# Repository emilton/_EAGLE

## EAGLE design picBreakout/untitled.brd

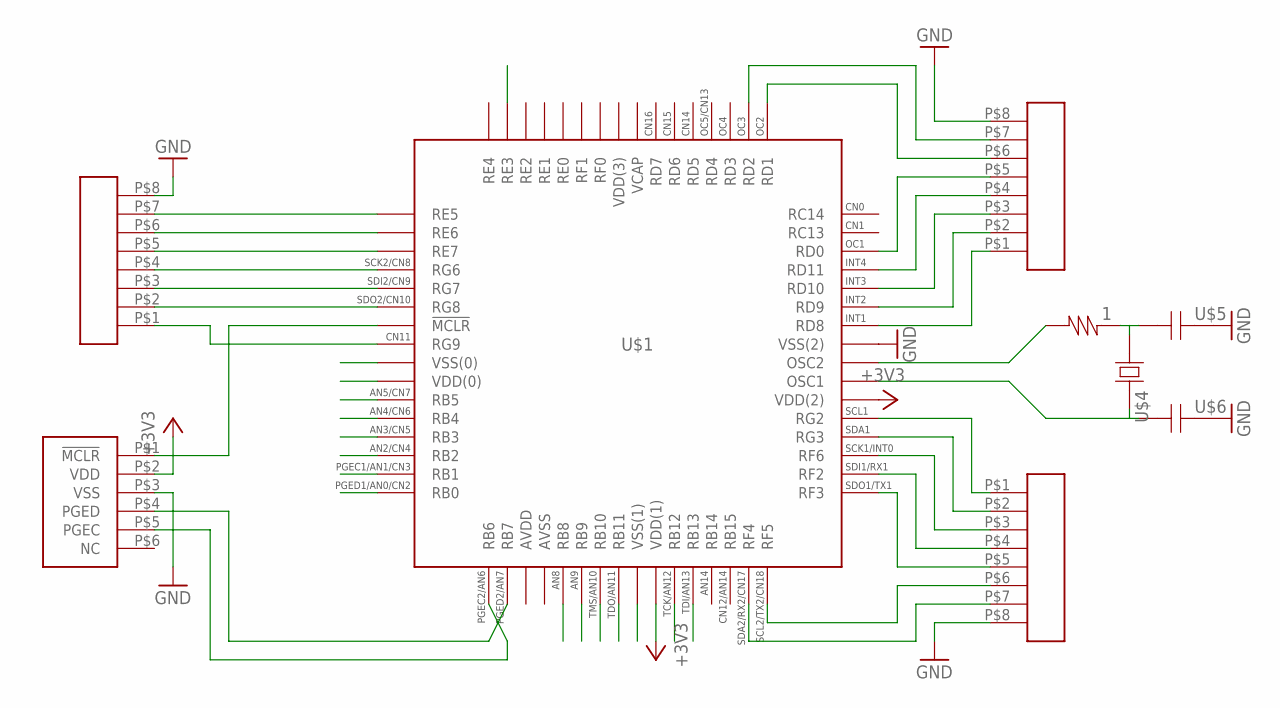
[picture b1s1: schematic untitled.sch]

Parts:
1: .RES-0603; E_0603
U$1: PIC32MX5XX; E_QFN64
U$2, U$3, U$27: CON_8PIN
U$4: .XTAL-CTS406; SMT_CRYSTAL
U$5, U$6: .CAP-0603; E_0603
U$29: CON_ICSP-PIC

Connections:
+3V3: U$1.P$26 (VDD(1)), U$1.P$38 (VDD(2)), U$29.P$2 (VDD)
GND: U$1.P$41 (VSS(2)), U$2.P$8, U$3.P$8, U$5.P$2, U$6.P$2, U$27.P$8, U$29.P$3 (VSS)
unnamed: U$1.P$37 (RG2), U$27.P$1
unnamed: U$1.P$36 (RG3), U$27.P$2
unnamed: U$1.P$35 (RF6), U$27.P$3
unnamed: U$1.P$42 (RD8), U$3.P$1
unnamed: U$1.P$18 (RB7), U$29.P$4 (PGED)
unnamed: U$1.P$6 (RG8), U$2.P$2
unnamed: U$1.P$5 (RG7), U$2.P$3
unnamed: U$1.P$43 (RD9), U$3.P$2
unnamed: U$1.P$44 (RD10), U$3.P$3
unnamed: U$1.P$34 (RF2), U$27.P$4
unnamed: U$1.P$33 (RF3), U$27.P$5
unnamed: U$1.P$32 (RF5), U$27.P$6
unnamed: U$1.P$4 (RG6), U$2.P$4
unnamed: U$1.P$3 (RE7), U$2.P$5
unnamed: U$1.P$49 (RD1), U$3.P$6
unnamed: U$1.P$50 (RD2), U$3.P$7
unnamed: U$1.P$31 (RF4), U$27.P$7
unnamed: U$1.P$45 (RD11), U$3.P$4
unnamed: U$1.P$46 (RD0), U$3.P$5
unnamed: U$1.P$17 (RB6), U$29.P$5 (PGEC)
unnamed: U$1.P$7 (!MCLR), U$29.P$1 (!MCLR)
unnamed: U$1.P$2 (RE6), U$2.P$6
unnamed: U$1.P$1 (RE5), U$2.P$7
unnamed: 1.P$1, U$1.P$40 (OSC2)
unnamed: 1.P$2, U$4.P$1, U$5.P$1
unnamed: U$1.P$39 (OSC1), U$4.P$3, U$6.P$1
unnamed: U$1.P$8 (RG9), U$2.P$1

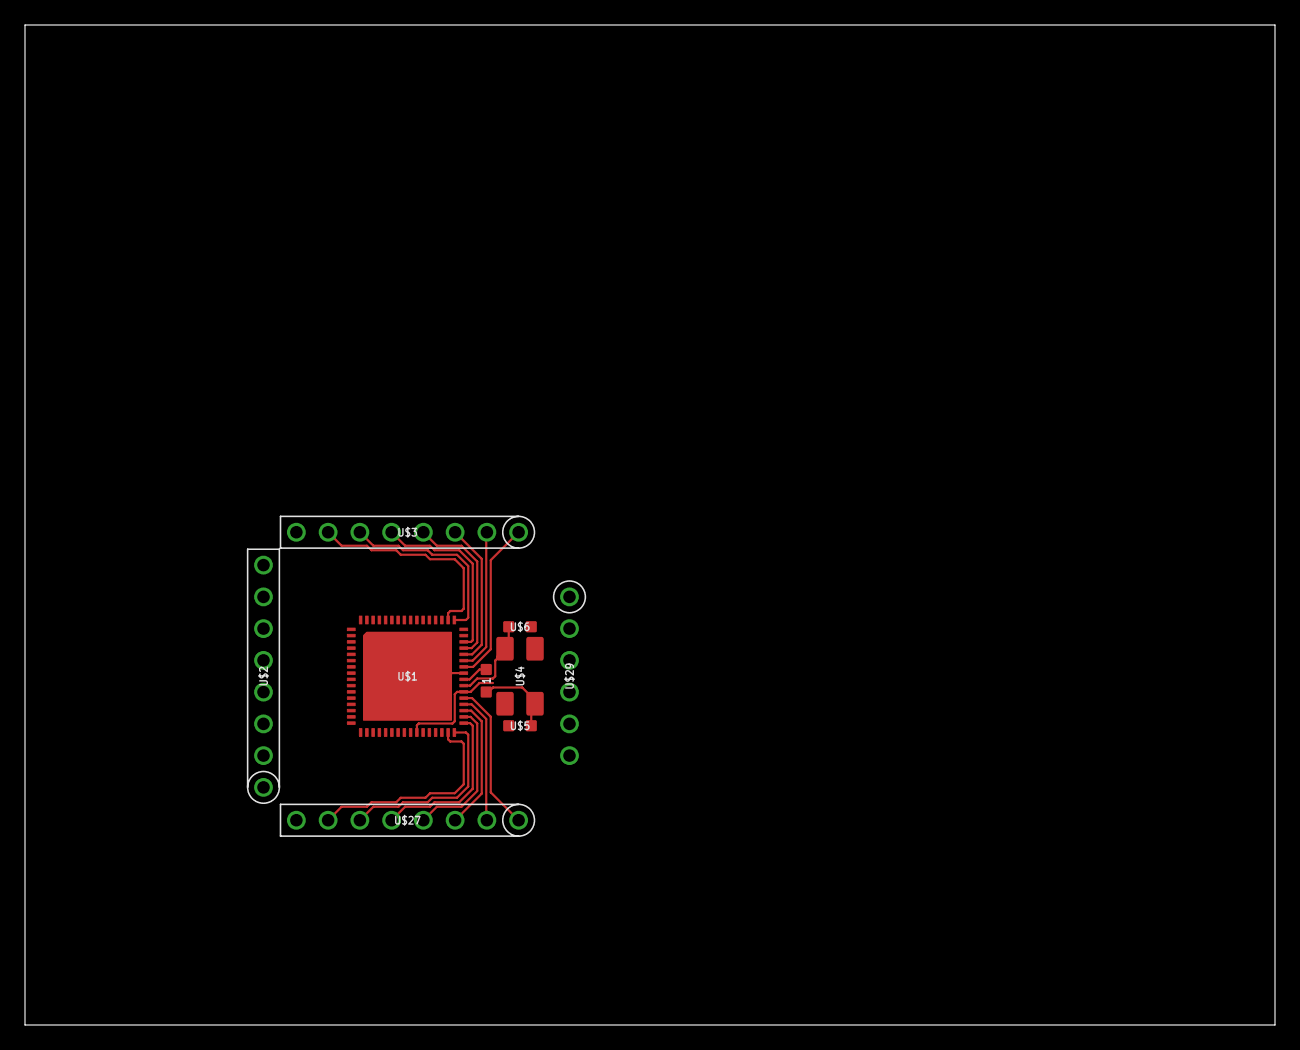
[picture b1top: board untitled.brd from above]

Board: 2 copper layers, 100.0 x 80.0 mm, 9 parts (0 on the bottom side), 29 nets.

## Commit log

2015-01-28 first commit
    Made basic components
2015-02-25 Still messing with the eagle library.
